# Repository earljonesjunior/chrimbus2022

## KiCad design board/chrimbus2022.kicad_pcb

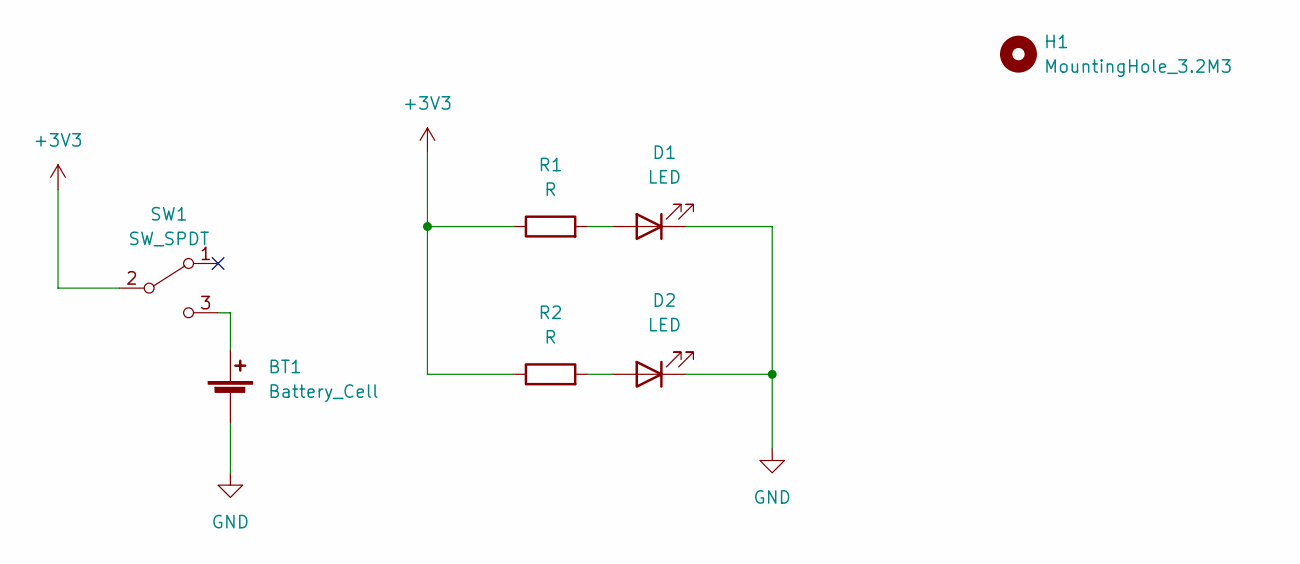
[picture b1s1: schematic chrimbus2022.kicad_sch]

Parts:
BT1: Battery_Cell; BatteryHolder_MPD_BC2003_1x2032
D1, D2: LED; Kingbright_AA3528
H1: MountingHole_3.2M3; MountingHole_3.2mm_M3
R1, R2: R; R_1206_3216Metric_Pad1.30x1.75mm_HandSolder
SW1: SW_SPDT; C&K_JS102011SCQN

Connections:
+3V3: R1.1, R2.1, SW1.2 (B)
GND: BT1.2 (-), D1.1 (K), D2.1 (K)
unnamed: D1.2 (A), R1.2
unnamed: D2.2 (A), R2.2
unnamed: BT1.1 (+), SW1.3 (C)

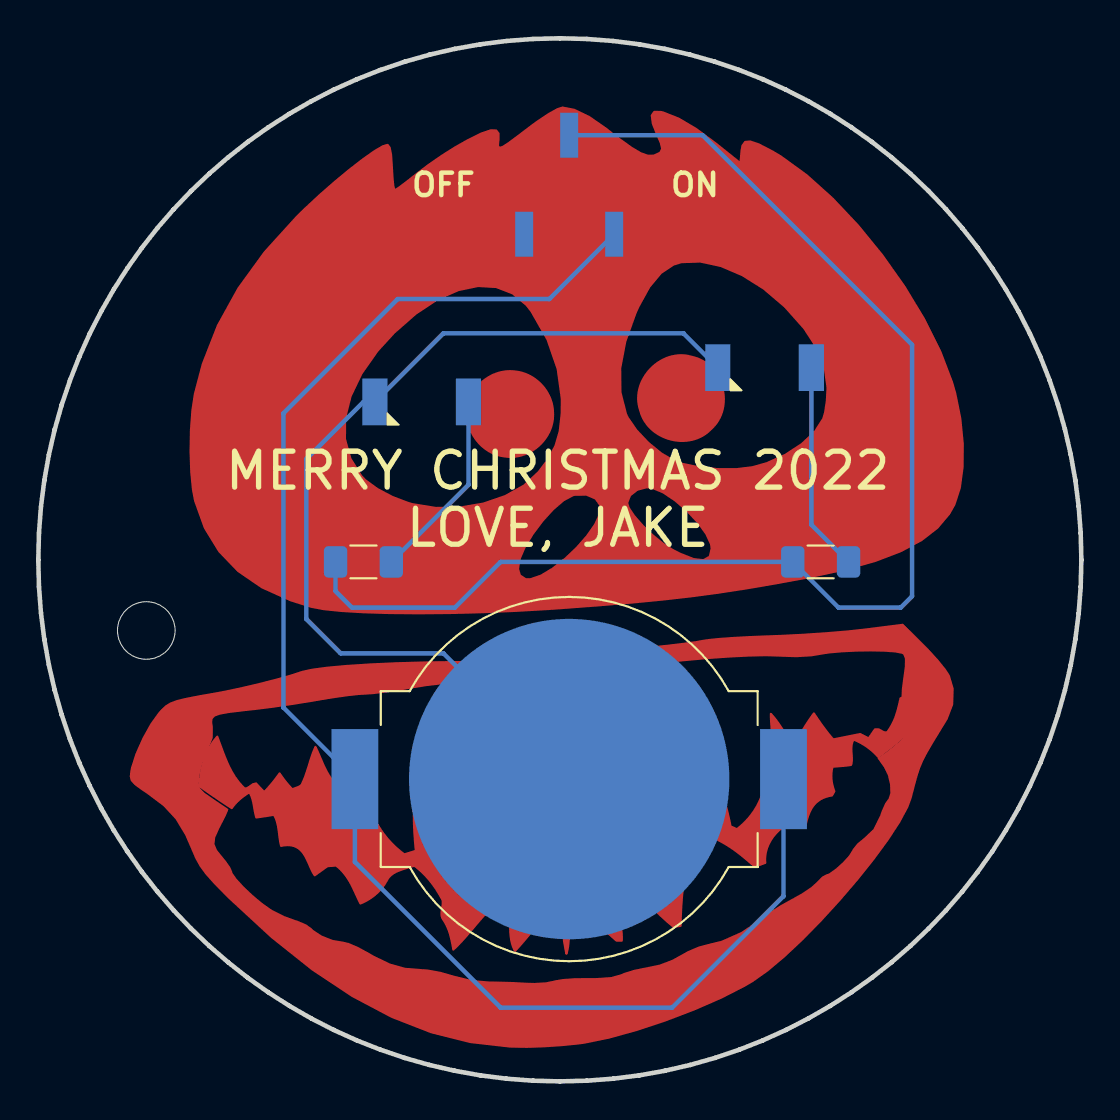
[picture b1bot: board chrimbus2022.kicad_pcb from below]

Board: 2 copper layers, 57.9 x 57.9 mm, 7 parts (7 on the bottom side), 5 nets.

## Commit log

2022-11-12 initial design
2022-11-15 board finalized
2023-06-10 backups
